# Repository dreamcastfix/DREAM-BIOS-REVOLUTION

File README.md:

# DREAM-BIOS-REVOLUTION
As part of the efforts to keep alive the projects that allow the Sega Dreamcast an alternative to optical readers, follow another project that I worked or was part of ... feel free to use the files at will.

The DREAM BIOS REVOLUTION project ALLOWS TO ADD AN ALTERNATIVE BIOS TO SEGA DREAMCAST

It is basically a board that transforms the PSOP 44 into TSOP48, in this case the pinout is based on the MX29LV160TMC-90 and MX29LV160DTBI-70G

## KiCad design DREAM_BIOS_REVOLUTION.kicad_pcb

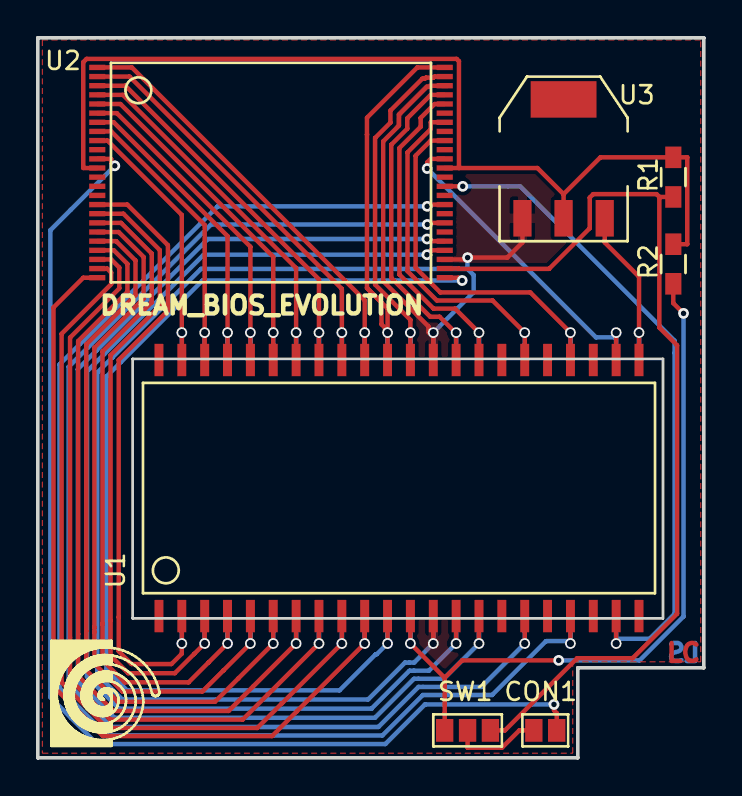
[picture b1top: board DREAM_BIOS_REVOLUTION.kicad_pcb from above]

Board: 2 copper layers, 37.0 x 40.0 mm, 8 parts (1 on the bottom side), 38 nets.

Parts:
CON1: CONN_01X02; GS2
R1, R2: 10K; R_0603_HandSoldering
SW1: SWITCH_INV; GS3
U1, U4: MX29LV160T/B; MX29_LV-160T-B_44-PIN
U2: MX29LV160T/B_48PIN; MX29_LV_160T-B_48-PIN
U3: LM1117; SOT-223

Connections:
/1: U1.35, U2.1, U4.10
/2: U1.36, U2.2, U4.9
/3: U1.37, U2.3, U4.8
/4: U1.38, U2.4, U4.7
/5: U1.39, U2.5, U4.6
/6: U1.40, U2.6, U4.5
/7: U1.41, U2.7, U4.4
/8: U1.42, U2.8, U4.3
/9: U1.43, U2.9, U4.2
/11: CON1.2, U2.11
/12: R1.1, R2.1, U2.12, U2.37, U3.2
/16: U1.2, U2.16, U4.43
/17: U1.3, U2.17, U4.42
/18: U1.4, U2.18, U4.41
/19: U1.5, U2.19, U4.40
/20: U1.6, U2.20, U4.39
/21: U1.7, U2.21, U4.38
/22: U1.8, U2.22, U4.37
/23: U1.9, U2.23, U4.36
/24: U1.10, U2.24, U4.35
/25: U1.11, U2.25, U4.34
/28: U1.14, U2.28, U4.31
/29: U1.15, U2.29, U4.30
/31: U1.17, U2.31, U4.28
/33: U1.19, U2.33, U4.26
/35: U1.21, U2.35, U4.24
/38: U1.24, U2.38, U4.21
/40: U1.26, U2.40, U4.19
/42: U1.28, U2.42, U4.17
/44: U1.30, U2.44, U4.15
/45: U1.31, U2.45, U4.14
/47: U1.33, U2.47, U4.12
/48: U1.34, U2.48, U4.11
/A1: U1.23, U3.3, U4.22
/D501: CON1.1, SW1.2
Earth: U1.13, U1.32, U2.27, U2.46, U3.1, U4.13, U4.32
PT2: R2.2, SW1.1, U1.12, U4.33
PT3: R1.2, SW1.3, U2.26
